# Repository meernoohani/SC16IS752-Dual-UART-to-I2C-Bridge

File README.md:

# SC16IS752 Dual UART to I2C Bridge

A high-performance bridge board based on the **SC16IS752**, designed to convert an I2C interface into two high-speed UART channels (up to 5 Mbps). This board is ideal for microcontrollers with limited hardware UARTS, such as when adding multiple sensors, GPS modules, or MIDI interfaces to your project. The PCB has been designed in KiCAD V.9.0 and the hardware has also been tested and verified. 

## 🛠 Features
* **Dual UART Channels:** Two independent UARTs (A and B) with 64-byte Send/Receive FIFOs.
* **I2C Interface:** Controlled via a single I2C bus, saving valuable MCU pins.
* **Onboard Crystal:** Integrated 14.7456 MHz crystal for precise baud rate generation.
* **Expanded GPIO:** Provides 8 additional programmable I/O pins (mapped to UART signals or general use).
* **Hardware Flow Control:** Full support for RTS/CTS signaling on both channels.
* **Address Selection:** Onboard jumpers (A0/A1) to easily change the I2C address.
* **Design Tool:** Created with **KiCad 9.0**.

## 📍 Pinout Overview
The board is logically organized for easy wiring:
* **Left Side:** I2C Bus (SCL/SDA), Power (3.3V/GND), and UART Channel A (TX/RX/RTS/CTS).
* **Right Side:** UART Channel B (TX/RX/RTS/CTS) and 8 General Purpose I/Os (GPIO0-GPIO7).
* **Bottom:** Address selection pads (A0, A1) and Interrupt (IRQ) output.

## ⚙️ Hardware Specifications
| Parameter | Value |
| :--- | :--- |
| **Supply Voltage** | 3.3V DC |
| **Crystal Frequency** | 14.7456 MHz |
| **Max Baud Rate** | 5 Mbps (at 3.3V) |
| **FIFO Size** | 64 Bytes per channel |
| **I2C Speed** | Up to 400 kHz (Fast-mode) |

## 📦 Production Files
The production-ready files are optimized for **JLCPCB** manufacturing and can be found in the `/JLCPCB Production Files & BOM` folder:
* Gerber and Drill files.
* BOM (Bill of Materials) with LCSC part numbers.
* CPL (Pick-and-Place) files for SMD assembly.

---
*Note: This project is shared for reference and educational purposes.*

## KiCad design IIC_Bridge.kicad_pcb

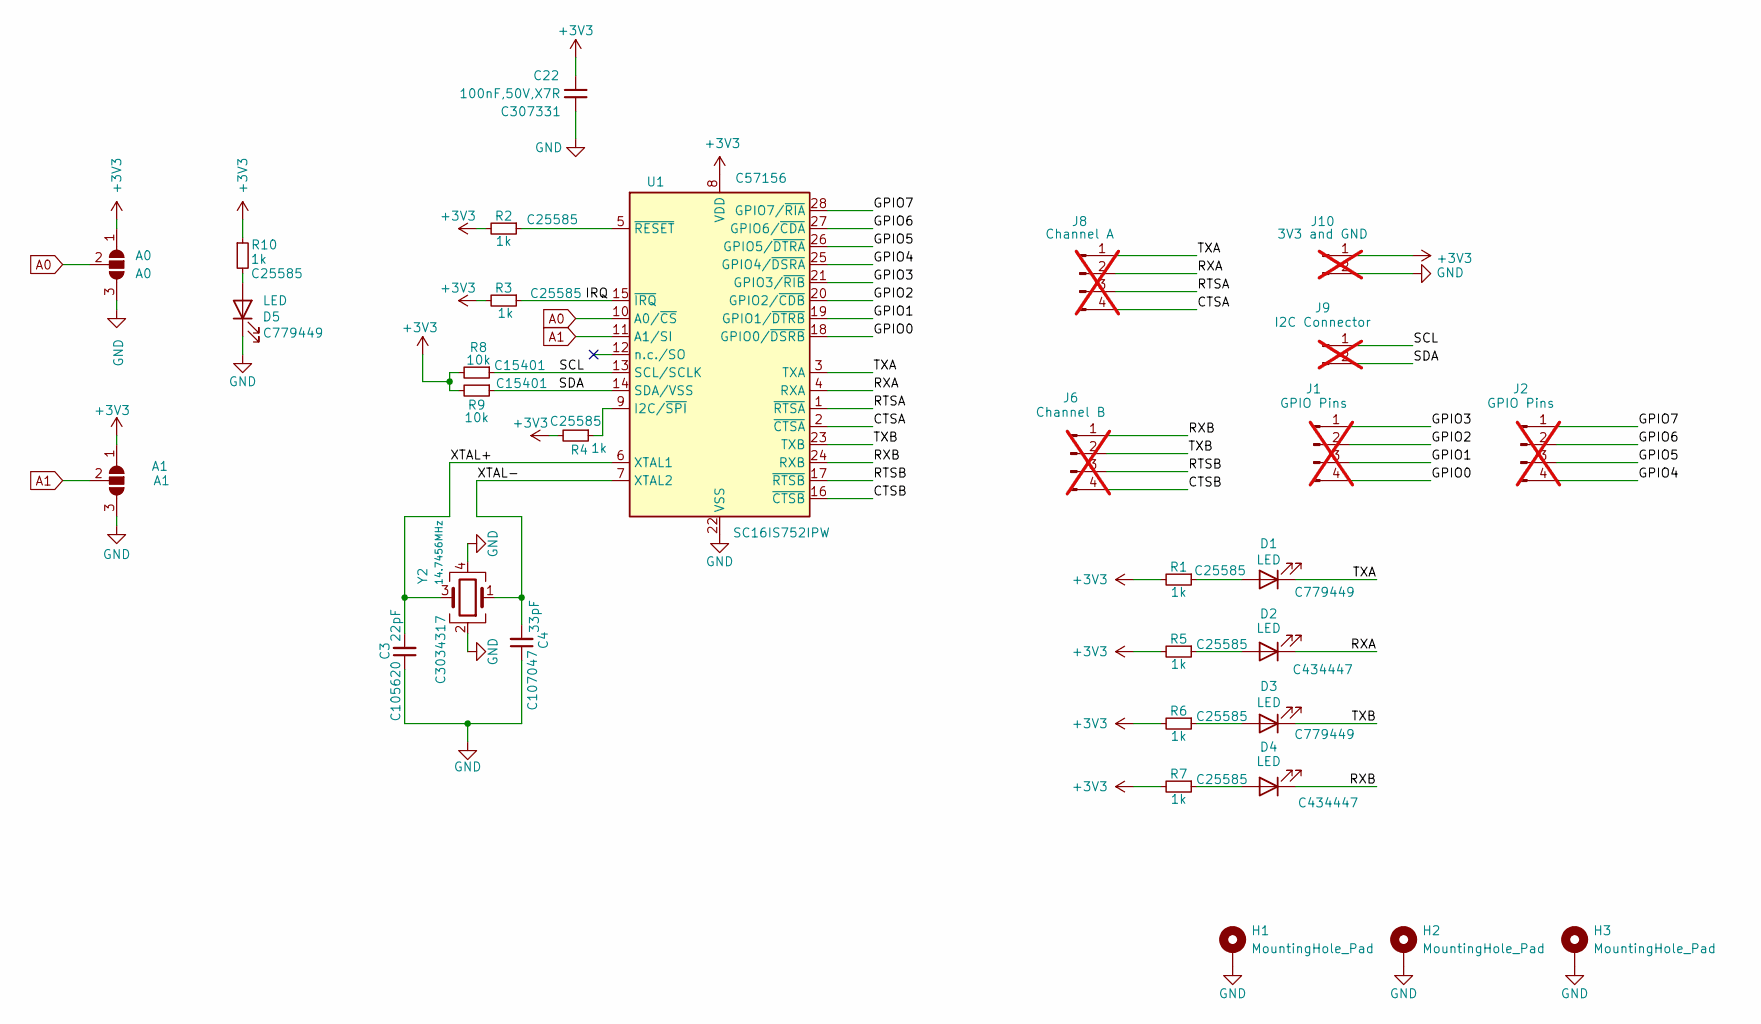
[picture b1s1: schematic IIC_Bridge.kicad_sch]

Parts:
A0: A0; SolderJumper-3_P1.3mm_Open_Pad1.0x1.5mm_NumberLabels
A1: A1; SolderJumper-3_P1.3mm_Open_Pad1.0x1.5mm_NumberLabels
C3: 22pF; C_0603_1608Metric; LCSC C105620
C4: 33pF; C_0603_1608Metric; LCSC C107047
C22: 100nF,50V,X7R; C_0402_1005Metric; MFGPN CL05B104KB54PNC; LCSC C307331
D1, D3, D5: LED; LED_0402_1005Metric; LCSC C779449
D2, D4: LED; LED_0402_1005Metric; LCSC C434447
H1, H2, H3: MountingHole_Pad; MountingHole_2.2mm_M2_ISO7380_Pad
J1, J2: GPIO Pins; PinHeader_1x04_P2.54mm_Vertical; not fitted
J6: Channel B; PinHeader_1x04_P2.54mm_Vertical; not fitted
J8: Channel A; PinHeader_1x04_P2.54mm_Vertical; not fitted
J9: I2C Connector; PinHeader_1x02_P2.54mm_Vertical; not fitted
J10: 3V3 and GND; PinHeader_1x02_P2.54mm_Vertical; not fitted
R1, R2, R3, R4, R5, R6, R7, R10: 1k; R_0603_1608Metric; LCSC C25585
R8, R9: 10k; R_0603_1608Metric; LCSC C15401
U1: SC16IS752IPW; TSSOP-28_4.4x9.7mm_P0.65mm; LCSC C57156
Y2: 14.7456MHz; Crystal_SMD_3225-4Pin_3.2x2.5mm; LCSC C3034317

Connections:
+3V3: A0.1 (A), A1.1 (A), C22.1, J10.1, R1.2, R2.2, R3.2, R4.2, R5.2, R6.2, R7.2, R8.2, R9.2, R10.1, U1.8 (VDD)
/CTSA: J8.4, U1.2 (~CTSA)
/CTSB: J6.4, U1.16 (~CTSB)
/GPIO0: J1.4, U1.18 (GPIO0/~DSRB)
/GPIO1: J1.3, U1.19 (GPIO1/~DTRB)
/GPIO2: J1.2, U1.20 (GPIO2/~CDB)
/GPIO3: J1.1, U1.21 (GPIO3/~RIB)
/GPIO4: J2.4, U1.25 (GPIO4/~DSRA)
/GPIO5: J2.3, U1.26 (GPIO5/~DTRA)
/GPIO6: J2.2, U1.27 (GPIO6/~CDA)
/GPIO7: J2.1, U1.28 (GPIO7/~RIA)
/IRQ: R3.1, U1.15 (~IRQ)
/RTSA: J8.3, U1.1 (~RTSA)
/RTSB: J6.3, U1.17 (~RTSB)
/RXA: D2.1 (K), J8.2, U1.4 (RXA)
/RXB: D4.1 (K), J6.1, U1.24 (RXB)
/SCL: J9.1, R8.1, U1.13 (SCL/SCLK)
/SDA: J9.2, R9.1, U1.14 (SDA/VSS)
/TXA: D1.1 (K), J8.1, U1.3 (TXA)
/TXB: D3.1 (K), J6.2, U1.23 (TXB)
/XTAL+: C3.2, U1.6 (XTAL1), Y2.3
/XTAL-: C4.2, U1.7 (XTAL2), Y2.1
A0: A0.2 (C), U1.10 (A0/~CS)
A1: A1.2 (C), U1.11 (A1/SI)
GND: A0.3 (B), A1.3 (B), C3.1, C4.1, C22.2, D5.1 (K), H1.1, H2.1, H3.1, J10.2, U1.22 (VSS), Y2.2, Y2.4
unnamed: D1.2 (A), R1.1
unnamed: D2.2 (A), R5.1
unnamed: D3.2 (A), R6.1
unnamed: D4.2 (A), R7.1
unnamed: D5.2 (A), R10.2
unnamed: R4.1, U1.9 (I2C/~SPI)
unnamed: R2.1, U1.5 (~RESET)

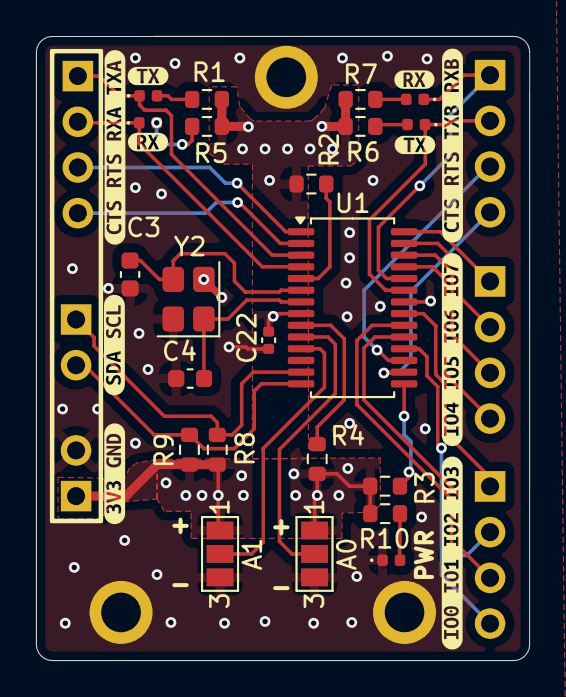
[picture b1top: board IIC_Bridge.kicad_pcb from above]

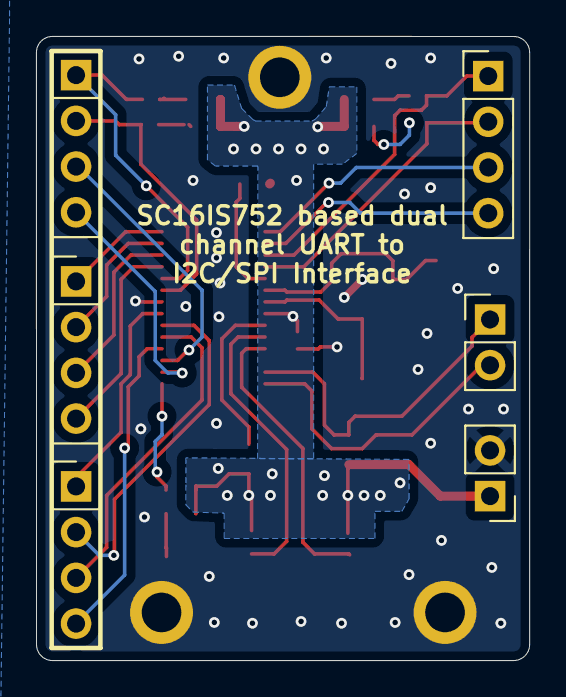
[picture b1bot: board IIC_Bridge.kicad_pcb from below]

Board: 2 copper layers, 27.4 x 34.7 mm, 41 parts (6 on the bottom side), 32 nets.

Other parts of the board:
kibuzzard-696A33C5: G***; kibuzzard-696A33C5
kibuzzard-696A33D3: G***; kibuzzard-696A33D3
kibuzzard-696A33E1: G***; kibuzzard-696A33E1
kibuzzard-696A37C2, kibuzzard-696A37C2#2: G***; kibuzzard-696A37C2
kibuzzard-696A37DE: G***; kibuzzard-696A37DE
kibuzzard-696A451F: G***; kibuzzard-696A451F
kibuzzard-696A3407: G***; kibuzzard-696A3407
kibuzzard-696A3458: G***; kibuzzard-696A3458
kibuzzard-696E1708: G***; kibuzzard-696E1708

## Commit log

2026-02-09 init
2026-02-09 Enhance README with project details and specifications
    Added detailed project description, features, pinout overview, hardware specifications, and production files information to README.md.
2026-02-21 Add LICENSE file
